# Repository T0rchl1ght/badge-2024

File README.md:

# OpenTaxus 

| Readme | [The Attribution Game](attribution) | [Trick or Treat Game](trickortreat) | [Badge Hardware](hardware) |
| ------------------- | --------------------------------------------- | --------------------------------------------- | ------------------------------------ |

Opentaxus is a permissively licensed set of hardware, software, and tooling to help as a starting point for customized conference badges.

## Motivation
Electronic conference badges are a well appreciated feature of an event, but very quickly become large, complicated projects. Typically there's custom hardware, custom embedded software, and sometimes much more. Every one of thos parts has the potential for schedule delays or causing the whole project to fail. Meanwhile, there's almost always a very hard deadline.

OpenTaxus is intended to get you started with a working system, allowing you to customize only as much as you want to or have time to. You are encouranged to use any or all of the parts of OpenTaxus for your own project

## Badge Games

There are currently two games for OpenTaxus. Each is in it's own subdirectory. Right now you'll just pick one (or make a new one) for your conference badge:

### [The Attribution Game](attribution)

Similar to the board game Clue or some versions of Carmen Sandiego,
you need to figure out who the threat actor, attack tool, and victim
are for each round of the game. You do this by trading cards (or
'clues') as well as your self-entered alibi name with others
at the conference.

The Attribution Game was designed for [LABScon 2023](https://www.labscon.io/) and then revised and improved for [BSidesSF 2024](https://bsidessf.org/)

### [Trick or Treat Game](trickortreat) 

In this game, you Trick-or-Treat, trading virtual candy with other conference attendees. Once you have collected enough, you can cash out your virtual candy for real candy or prizes.

The Trick or Treat Game was designed for [BSidesPDX 2024](https://bsidespdx.org/)

## Repo Contents

This repository contains the hardware and software for the badge and multiple games. We hope it is useful for those who wish to hack the badges and game, anyone who wants to use the badge to learn some circuitpython, as well as others who might like to reuse some or all of it for other projects.

The badge hardware was designed and produced by @securityfitz, with variants being used for BSidesSF 2024 and Labscon.
The badge software is a fork of the Labscon badge software, further mangled by @rlc4, @lanrat, and @securelyfitz, and then further forked and mangled by *

## Event Badge Designer Instructions

OpenTaxus is intended to be be a drop-in electronic badge that works from the start. While you can use the badge as it's presented here if you plan to use it for an event or organization, you may want to customize the appearance of the badge, and possibly some of the text and programming. 

### Suggested customizations:
	
#### Physical Appearance:
* Add custom artwork such as your logo to the badges KiCad files (found in the [hardware](/hardware) folder). 
* Add in the name of the artist and contributors to the silkscreen.
* Include the repo for your code or events in the silkscreen on the back of the badge.

#### Electronic text:
* The Attribution Game has a number of custom strings that can be adjusted within the [genfiles.py](./attribution/configs/genfiles.py) file. In particular, you may want to change line 121 to say the name of your event or organization instead of "A mysterious group".
* The same file also includes other bits of flavor text that could be customized to match your event's theme or location.
* Changing the menu text of the badge to show your event name instead of "OpenTaxus" can be done on lines 23 and 139 of [home.py](./attribution/software/home.py)
* Sponsor names can be added within [home.py](./attribution/software/home.py) around line 144.

#### Misc:
* You may also want to change the file that you're reading now ([README.md](README.md)) to welcome your attendee's, ctf players, etc.

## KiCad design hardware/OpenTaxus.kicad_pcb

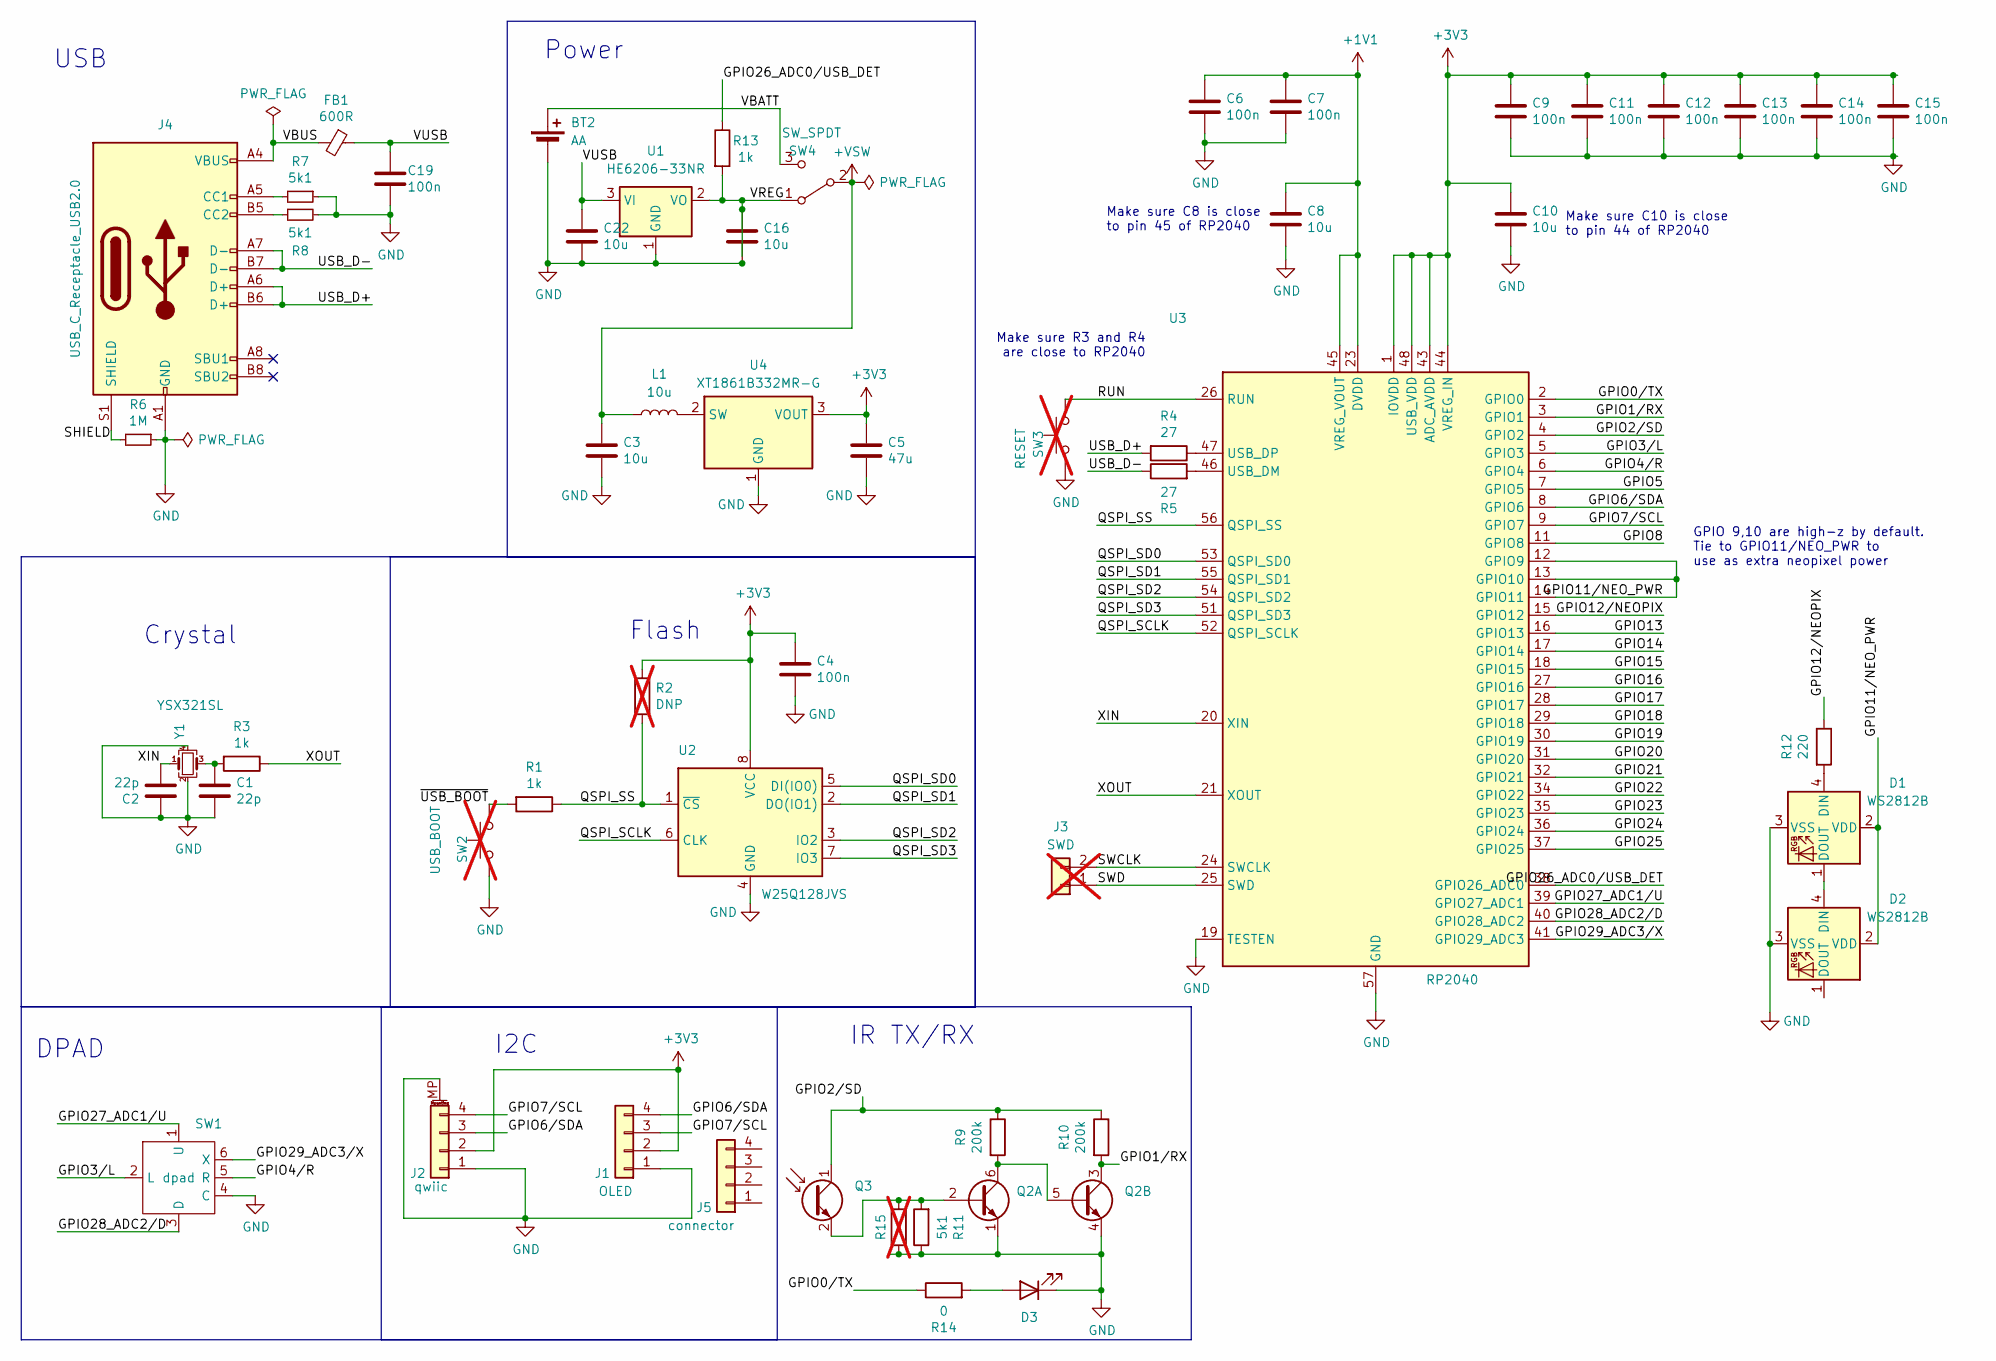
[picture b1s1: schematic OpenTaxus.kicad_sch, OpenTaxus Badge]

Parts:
BT2: AA; BatteryHolder_Keystone_2460_1xAA; LCSC C5290181
C1, C2: 22p; C_0402_1005Metric; LCSC C106203
C3, C8, C10, C16, C22: 10u; C_0402_1005Metric; LCSC C15525
C4, C6, C7, C9, C11, C12, C13, C14, C15, C19: 100n; C_0402_1005Metric; LCSC C100072
C5: 47u; C_0805_2012Metric; LCSC C16780
D1, D2: WS2812B; LED_WS2812B_PLCC4_1.0x1.0mm; LCSC C5349953
D3: IR12-21C/TR8; IR12-21C-TR8; LCSC C53672
FB1: 600R; L_0402_1005Metric; LCSC C76886
J1: OLED; PinHeader_1x04_P2.54mm_Vertical; LCSC C5248080
J2: qwiic; JST_SH_SM04B-SRSS-TB_1x04-1MP_P1.00mm_Horizontal; LCSC C7433425
J3: SWD; SolderJumper-2_P1.3mm_Open_RoundedPad1.0x1.5mm; LCSC DNP; not fitted
J4: USB_C_Receptacle_USB2.0; USB_C_Receptacle_HRO_TYPE-C-31-M-12; LCSC C2927038
J5: connector; PinHeader_1x04_P2.54mm_Vertical; LCSC C2902691
L1: 10u; L_1008_2520Metric; LCSC C602018
Q2: BC847BS; SOT-363_SC-70-6; LCSC C5380687
Q3: PT12-21B/TR8; PT12-21B-TR8; LCSC C264383
R1, R3, R13: 1k; R_0402_1005Metric; LCSC C11702
R2, R15: DNP; R_0402_1005Metric; LCSC DNP; not fitted
R4, R5: 27; R_0402_1005Metric; LCSC C25100
R6: 1M; R_0402_1005Metric; LCSC C26083
R7, R8, R11: 5k1; R_0402_1005Metric; LCSC C25941
R9, R10: 200k; R_0402_1005Metric; LCSC C25764
R12: 220; R_0402_1005Metric; LCSC C25091
R14: 0; R_0402_1005Metric; LCSC C17168
SW1: dpad; 10x10x10x9-6P-WX; LCSC C2858290
SW2: USB_BOOT; SolderJumper-2_P1.3mm_Open_RoundedPad1.0x1.5mm; LCSC DNP; not fitted
SW3: RESET; SolderJumper-2_P1.3mm_Open_RoundedPad1.0x1.5mm; LCSC DNP; not fitted
SW4: SW_SPDT; SW_SPDT_PCM12; LCSC C319020
U1: HE6206-33NR; SOT-23-3; LCSC C5199441
U2: W25Q128JVS; SOIC-8_5.23x5.23mm_P1.27mm; LCSC C97521
U3: RP2040; QFN-56-1EP_7x7mm_P0.4mm_EP3.2x3.2mm; LCSC C2040
U4: XT1861B332MR-G; SOT-23; LCSC C236396
Y1: YSX321SL; Crystal_SMD_3225-4Pin_3.2x2.5mm; LCSC C9002

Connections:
+1V1: C6.1, C7.1, C8.1, U3.23 (DVDD), U3.45 (VREG_VOUT), U3.50 (DVDD)
+3V3: C4.1, C5.1, C9.1, C10.1, C11.1, C12.1, C13.1, C14.1, C15.1, J1.2, J2.2, R2.1, U2.8 (VCC), U3.1 (IOVDD), U3.10 (IOVDD), U3.22 (IOVDD), U3.33 (IOVDD), U3.42 (IOVDD), U3.43 (ADC_AVDD), U3.44 (VREG_IN), U3.48 (USB_VDD), U3.49 (IOVDD), U4.3 (VOUT)
+VSW: C3.1, L1.1, SW4.2 (B)
/GPIO0/TX: R14.1, U3.2 (GPIO0)
/GPIO1/RX: Q2.3 (C2), R10.2, U3.3 (GPIO1)
/GPIO2/SD: Q3.1 (C), R9.1, R10.1, U3.4 (GPIO2)
/GPIO3/L: SW1.2 (L), U3.5 (GPIO3)
/GPIO4/R: SW1.5 (R), U3.6 (GPIO4)
/GPIO5: U3.7 (GPIO5)
/GPIO6/SDA: J1.4, J2.3, U3.8 (GPIO6)
/GPIO7/SCL: J1.3, J2.4, U3.9 (GPIO7)
/GPIO8: U3.11 (GPIO8)
/GPIO11/NEO_PWR: D1.2 (VDD), D2.2 (VDD), U3.12 (GPIO9), U3.13 (GPIO10), U3.14 (GPIO11)
/GPIO12/NEOPIX: R12.1, U3.15 (GPIO12)
/GPIO13: U3.16 (GPIO13)
/GPIO14: U3.17 (GPIO14)
/GPIO15: U3.18 (GPIO15)
/GPIO16: U3.27 (GPIO16)
/GPIO17: U3.28 (GPIO17)
/GPIO18: U3.29 (GPIO18)
/GPIO19: U3.30 (GPIO19)
/GPIO20: U3.31 (GPIO20)
/GPIO21: U3.32 (GPIO21)
/GPIO22: U3.34 (GPIO22)
/GPIO23: U3.35 (GPIO23)
/GPIO24: U3.36 (GPIO24)
/GPIO25: U3.37 (GPIO25)
/GPIO26_ADC0/USB_DET: R13.1, U3.38 (GPIO26_ADC0)
/GPIO27_ADC1/U: SW1.1 (U), U3.39 (GPIO27_ADC1)
/GPIO28_ADC2/D: SW1.3 (D), U3.40 (GPIO28_ADC2)
/GPIO29_ADC3/X: SW1.6 (X), U3.41 (GPIO29_ADC3)
/QSPI_SCLK: U2.6 (CLK), U3.52 (QSPI_SCLK)
/QSPI_SD0: U2.5 (DI(IO0)), U3.53 (QSPI_SD0)
/QSPI_SD1: U2.2 (DO(IO1)), U3.55 (QSPI_SD1)
/QSPI_SD2: U2.3 (IO2), U3.54 (QSPI_SD2)
/QSPI_SD3: U2.7 (IO3), U3.51 (QSPI_SD3)
/QSPI_SS: R1.1, R2.2, U2.1 (~CS), U3.56 (QSPI_SS)
/RUN: SW3.1, U3.26 (RUN)
/SHIELD: J4.S1 (SHIELD), R6.2
/SWCLK: J3.2, U3.24 (SWCLK)
/SWD: J3.1, U3.25 (SWD)
/USB_D+: J4.A6 (D+), J4.B6 (D+), R4.2
/USB_D-: J4.A7 (D-), J4.B7 (D-), R5.1
/VBATT: BT2.1 (+), SW4.3 (C)
/VBUS: FB1.2, J4.A4 (VBUS), J4.A9 (VBUS), J4.B4 (VBUS), J4.B9 (VBUS)
/VREG: C16.1, R13.2, SW4.1 (A), U1.2 (VO)
/VUSB: C19.1, C22.1, FB1.1, U1.3 (VI)
/XIN: C2.2, U3.20 (XIN), Y1.1
/XOUT: R3.1, U3.21 (XOUT)
/~USB_BOOT: R1.2, SW2.1
GND: BT2.2 (-), C1.2, C2.1, C3.2, C4.2, C5.2, C6.2, C7.2, C8.2, C9.2, C10.2, C11.2, C12.2, C13.2, C14.2, C15.2, C16.2, C19.2, C22.2, D1.3 (VSS), D2.3 (VSS), D3.2 (K), J1.1, J2.1, J2.MP (MountPin), J4.A1 (GND), J4.A12 (GND), J4.B1 (GND), J4.B12 (GND), Q2.1 (E1), Q2.4 (E2), R6.1, R7.1, R8.2, R11.1, R15.1, SW1.4 (C), SW2.2, SW3.2, U1.1 (GND), U2.4 (GND), U3.19 (TESTEN), U3.57 (GND), U4.1 (GND), Y1.2, Y1.4
unnamed: C1.1, R3.2, Y1.3
unnamed: D1.4 (DIN), R12.2
unnamed: D1.1 (DOUT), D2.4 (DIN)
unnamed: D3.1 (A), R14.2
unnamed: J4.A5 (CC1), R7.2
unnamed: J4.B5 (CC2), R8.1
unnamed: Q2.2 (B1), Q3.2 (E), R11.2, R15.2
unnamed: Q2.5 (B2), Q2.6 (C1), R9.2
unnamed: R5.2, U3.46 (USB_DM)
unnamed: R4.1, U3.47 (USB_DP)
unnamed: L1.2, U4.2 (SW)

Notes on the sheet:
DPAD
Make sure C10 is close to pin 44 of RP2040
Make sure C8 is close to pin 45 of RP2040
IR TX/RX
USB
I2C
Make sure R3 and R4 are close to RP2040
Flash
Crystal
Power
GPIO 9,10 are high-z by default. Tie to GPIO11/NEO_PWR to use as extra neopixel power

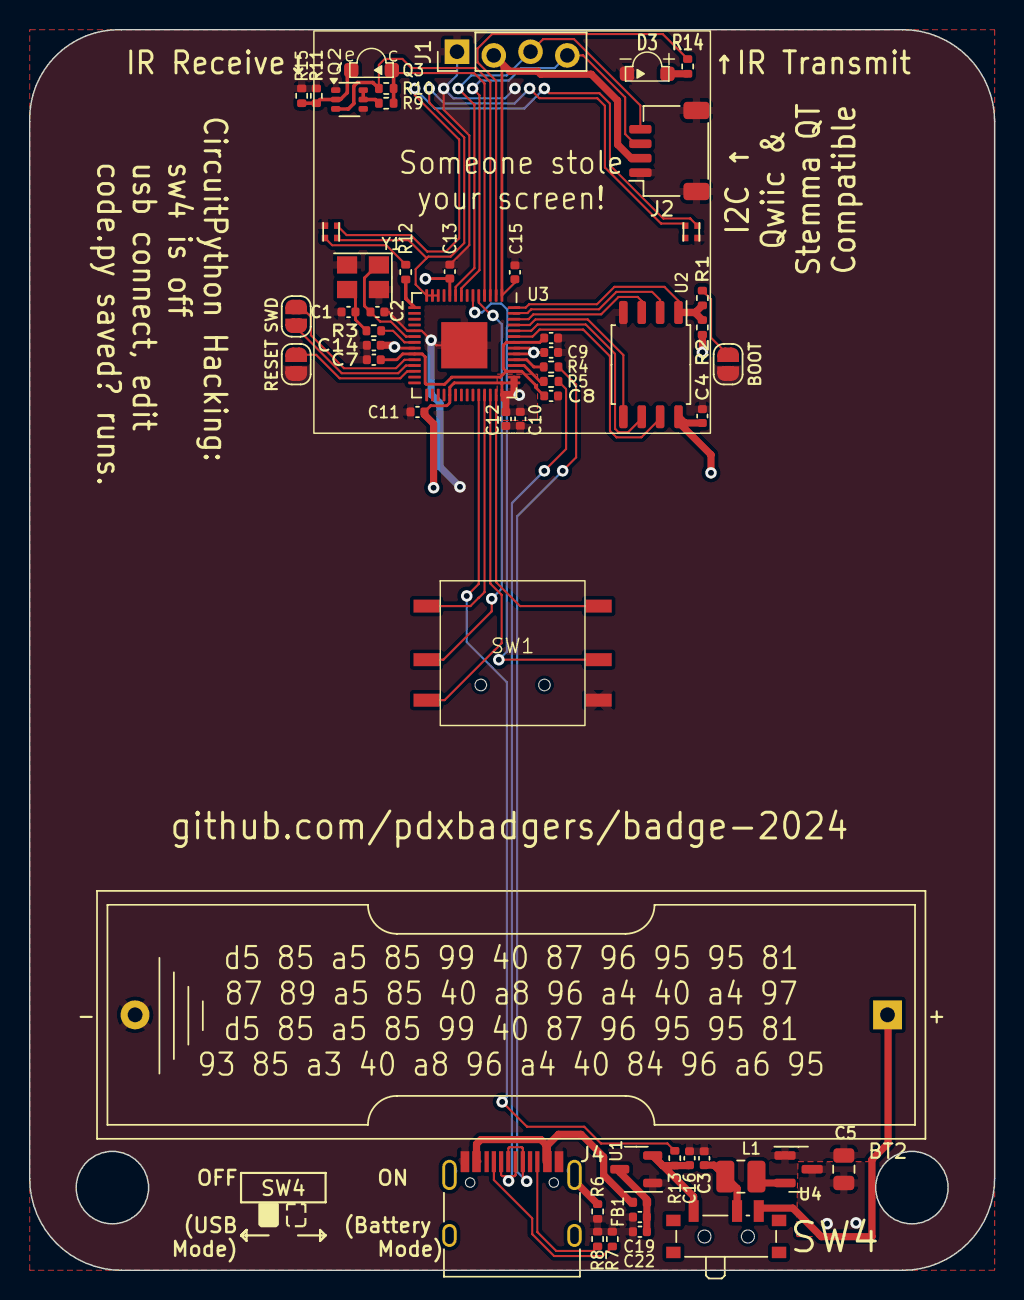
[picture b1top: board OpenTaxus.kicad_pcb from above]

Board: 2 copper layers, 66.7 x 85.7 mm, 54 parts (0 on the bottom side), 47 nets.

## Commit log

2024-08-30 adding bsidespdx logo to badge
2024-08-30 remove unused i2c header
2024-08-30 fine tune via locaions to be hidden by black soldermask
2024-09-27 changing readme and file setup preparing for a second game
2024-09-27 fix typos and links
2024-09-27 Relinking the sub-readmes and adding a few details
2024-09-27 minor settings tweak for bom and bsidespdx artwork
2024-09-27 adding trickortreat readme
2024-10-08 Adding in existing ToT and badge code
2024-10-19 moving code into badge; removing poc code
2024-10-20 adding keyboard entry; cleaning up home.py OOBE messages
2024-10-20 making friends out of alibis
2024-10-20 jinkies, a candy!
2024-10-20 fixing alibi->friend in friends.py
2024-10-20 cleanup on clues->candy and alibis->friends changesy
2024-10-20 clean up unused code commented out
2024-10-20 moving dock to hardware; ignoring generated .json files
2024-10-20 removing pub.json
2024-10-20 adding genfiles for trick-or-treat with json and nice enhancements
2024-10-20 removing badge-specific files and adding to gitignore
2024-10-20 first pass of genfiles and flasher for trickortreaty
2024-10-20 added candy assignments to genfiles.py
2024-10-20 one more clue->candy swap
2024-10-20 merging genfiles and flash
2024-10-21 Switch over game data structure to trick or treat, with json
2024-10-21 adding an obfuscated string for reasons
2024-10-21 adding extra rows in list option
2024-10-22 persisting selection in a display list when possible
2024-10-22 fixing display layout for now; needs some refactoring
2024-10-22 consolidating similar code
2024-10-22 adding candy tally
2024-10-22 implementing candy display
2024-10-22 replaced curTopRow with selTopRow, only in gettextselect
2024-10-22 fixed wrong candy name displayed on console
2024-10-22 fixing up friends list with test data
2024-10-22 handle zero candy condition gracefully
2024-10-22 handle zero friends condition gracefully
2024-10-22 clean up settings screen and game structure
2024-10-23 add the 'nuke' cmd line parameter to nuke first badge then go back to normal
2024-10-23 clean up and streamline trade for trick or treat
2024-10-23 removing unused bmp
2024-10-23 updating and simplifying trade for new trick or treat game.py
2024-10-23 bugfixes to support changes to trade.py
2024-10-23 reording so that game data is instantiated first, then all the display pages
2024-10-23 trimming down home screen, sponsors to settings, display user info
2024-10-23 fixed string index method not available in circuitpython
2024-10-23 adding BsidesPDX sponsors
2024-10-23 clearing old 'sponsors' string
2024-10-23 display typo
2024-10-24 fixing mistaken extra comment
2024-10-24 clean up ui, change candy numbering scheme
2024-10-24 finishing touches on strings
2024-10-24 upping badge count
2024-10-24 Implemented Validation code
    Will review in morning
2024-10-24 added comments for Smiley0x1
2024-10-24 fixes contriubted by Smiley0x1
2024-10-25 refactoring some code, logging files, and calculating payouts
2024-10-25 adding cleanup command note
